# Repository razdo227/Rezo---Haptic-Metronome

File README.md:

# Rezo — Haptic Metronome

A hardware + firmware + mobile app capstone project for a wearable haptic metronome.

## Architecture (at a glance)

```text
Mobile App (Expo / React Native)
  └─ Controls: BPM, transport, sync mode, tap tempo, vibration type
  └─ Sync Modes: INTERNAL | MIDI_CLOCK | MIDI_BEAT
            │
            ├── BLE GATT
            │
Desktop Plugin (JUCE VST3/AU) + Rezo Helper
  └─ DAW transport -> helper IPC -> BLE GATT
  └─ Defaults device mode to MIDI_CLOCK on desktop connect
            │
            ▼
nRF52840 wearable firmware
  └─ Real-time haptic scheduler
  └─ INTERNAL / MIDI_CLOCK / MIDI_BEAT runtime modes
  └─ Dual-LRA drive path (DRV2605L x2)
  └─ Side routing + polyrhythm scheduling
            │
            ▼
Custom PCB + wearable enclosure
```

## Repo layout

- `app/` — cross-platform app (Expo/React Native)
  - `app/src/screens/MainScreen.tsx` — main device-control UI
  - `app/src/context/DeviceContext.tsx` — BLE state + status parsing
  - `app/src/services/BLEService.ts` — BLE transport
  - `app/src/lib/tempo.ts` — tap/BPM logic
  - `app/tests/` — unit tests (Vitest)
- `Kicad Schematics/` — schematic, PCB, and DRC/ERC outputs
- `firmware/` — nRF firmware scaffold + Arduino-ready sketch
- `rezo-plugin/` — JUCE desktop plugin, helper app, and tests
  - `rezo-plugin/Source/` — plugin, helper, BLE bridge, and UI code
  - `rezo-plugin/Tests/` — Catch2 protocol and transport tests
  - `rezo-plugin/JUCE/` — JUCE submodule
- `fab/` — manufacturing files (Gerbers, drill, ZIP)
- `docs/` — project specs, workflows, and engineering notes

## Current status

- App: BLE control surface for INTERNAL / MIDI_CLOCK / MIDI_BEAT modes; `SIDE`/`POLY` commands wired up
- Firmware: dual-LRA scheduler; DRV2605L auto-calibrated for Vybronics VLV101040A; 16 defined waveform patterns
- Desktop: JUCE VST3/AU plugin; 7 presets now match mobile display names; unified via `GATTConstants.h`
- Tests: app unit tests and plugin Catch2 suite
- PCB: v0.1 DRC cleaned to non-critical warnings + Gerbers exported

## Build matrix

| Workstream | Status | Notes |
|---|---|---|
| Mobile App | In Progress | BLE control path is in place; desktop parity still ongoing |
| Firmware | In Progress | Desktop/app protocol implemented; hardware tuning continues |
| Desktop Plugin | In Progress | Helper-based BLE path working in DAWs |
| PCB (v0.1) | In Progress | DRC stabilized; fabrication files generated |
| Validation | In Progress | Unit tests passing; HIL tests pending |
| Research Study | Planned | Protocol and analysis pipeline outlined |

## Run app locally

```bash
cd app
npm install
npm run start
```

## Validate app logic

```bash
cd app
npm test
npx tsc --noEmit
```

## Build desktop plugin

```bash
cd rezo-plugin
cmake -S . -B build/debug -DCMAKE_BUILD_TYPE=Debug
cmake --build build/debug --config Debug
ctest --test-dir build/debug -C Debug --output-on-failure
```

## Next priorities

1. Add app-side UI controls for side routing and polyrhythms (commands wired, UI pending).
2. Hardware-in-loop tests for timing jitter and haptic response.
3. Publish the desktop/helper workflow and host compatibility notes.
4. Validate LRA auto-calibration results on hardware (check `A_CAL_COMP`/`A_CAL_BEMF` registers post-boot).

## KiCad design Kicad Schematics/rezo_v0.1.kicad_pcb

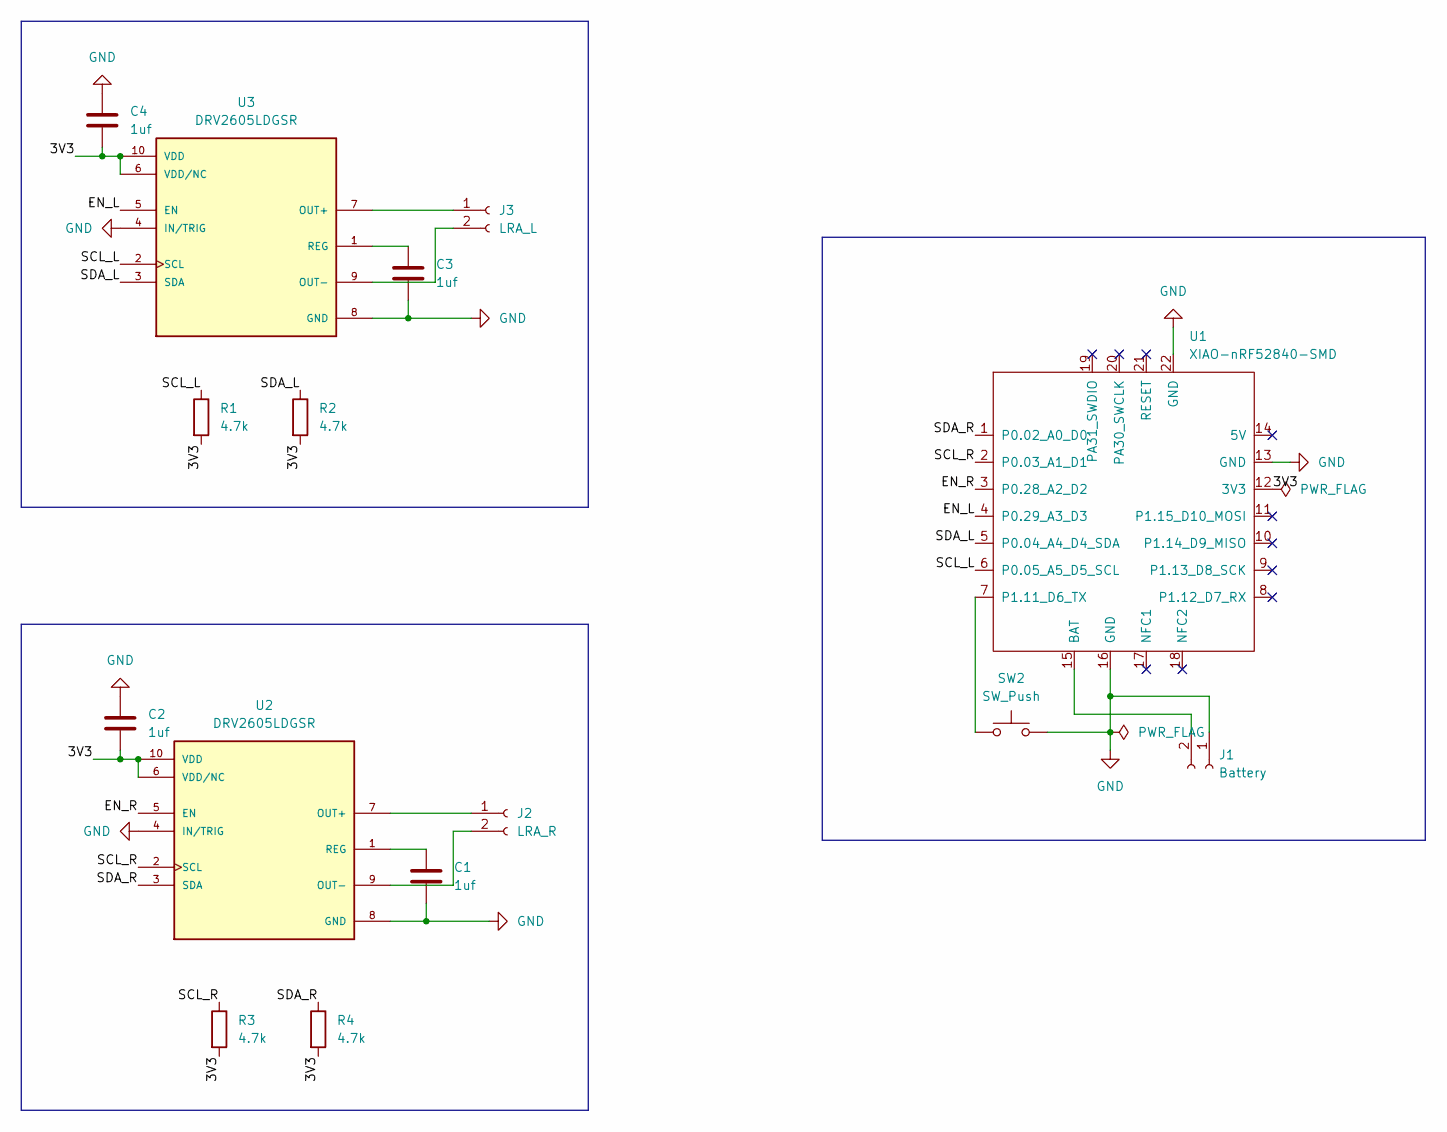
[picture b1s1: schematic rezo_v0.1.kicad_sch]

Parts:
C1, C2, C3, C4: 1uf; C_0603_1608Metric
J1: Battery; SolderWire-0.1sqmm_1x02_P3.6mm_D0.4mm_OD1mm
J2: LRA_R; BOURNS_70AAJ-2-M0
J3: LRA_L; BOURNS_70AAJ-2-M0
R1, R2, R3, R4: 4.7k; R_0603_1608Metric
SW2: SW_Push; SW_SPST_B3S-1000
U1: XIAO-nRF52840-SMD
U2, U3: DRV2605LDGSR; PARTREV D

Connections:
/3V3: C2.2, C4.2, R1.2, R2.2, R3.2, R4.2, U1.12 (3V3), U2.6 (VDD/NC), U2.10 (VDD), U3.6 (VDD/NC), U3.10 (VDD)
/EN_L: U1.4 (P0.29_A3_D3), U3.5 (EN)
/EN_R: U1.3 (P0.28_A2_D2), U2.5 (EN)
/SCL_L: R1.1, U1.6 (P0.05_A5_D5_SCL), U3.2 (SCL)
/SCL_R: R3.1, U1.2 (P0.03_A1_D1), U2.2 (SCL)
/SDA_L: R2.1, U1.5 (P0.04_A4_D4_SDA), U3.3 (SDA)
/SDA_R: R4.1, U1.1 (P0.02_A0_D0), U2.3 (SDA)
GND: C1.2, C2.1, C3.2, C4.1, J1.1, SW2.2, U1.13 (GND), U1.16 (GND), U1.22 (GND), U2.4 (IN/TRIG), U2.8 (GND), U3.4 (IN/TRIG), U3.8 (GND)
unnamed: J1.2, U1.15 (BAT)
unnamed: J2.1, U2.7 (OUT+)
unnamed: J2.2, U2.9 (OUT-)
unnamed: J3.1, U3.7 (OUT+)
unnamed: J3.2, U3.9 (OUT-)
unnamed: SW2.1, U1.7 (P1.11_D6_TX)
unnamed: C1.1, U2.1 (REG)
unnamed: C3.1, U3.1 (REG)

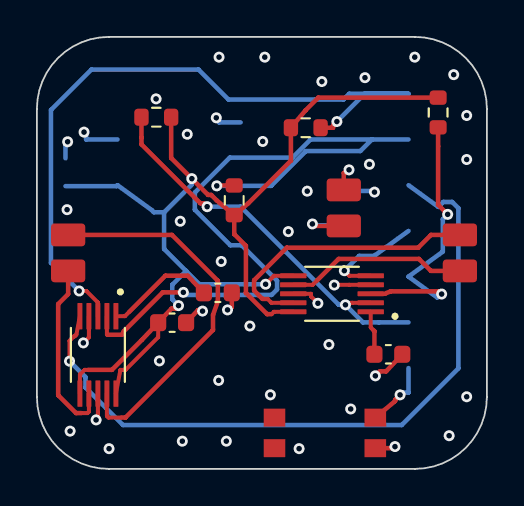
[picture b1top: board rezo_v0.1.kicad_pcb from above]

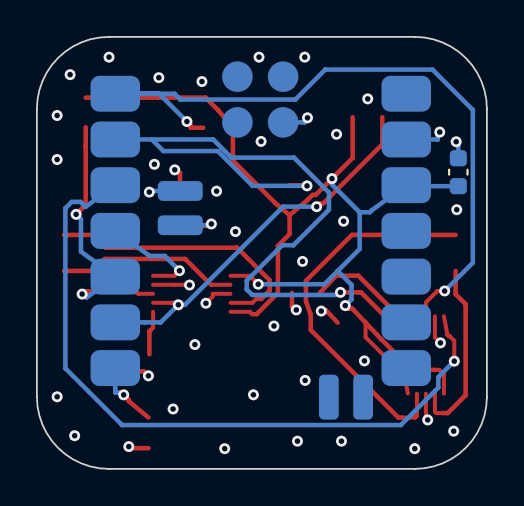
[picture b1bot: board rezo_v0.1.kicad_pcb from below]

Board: 4 copper layers, 25.0 x 24.0 mm, 15 parts (2 on the bottom side), 16 nets.

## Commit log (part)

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2026-01-13 Update project title format in README
2026-01-13 Update project title in README
2026-03-03 Add project operating system and fact-check protocol
2026-03-03 Add KiCad schematic/PCB next-step checklist for v0.2
2026-03-03 Add v0.1 2-layer/4-layer KiCad + JLC manufacturing playbook
2026-03-04 Tune KiCad DRC constraints and mask settings; generate DRC/ERC reports
2026-03-04 Clean silkscreen DRC warnings; reduce board DRC to library-only warnings
2026-03-11 Scaffold cross-platform app v0.1 and add firmware+app feature spec with mic tap tempo
2026-03-11 Add BLE/MIDI/mic-ready app architecture with tested tempo, MIDI clock, and onset logic
2026-03-11 Remove node_modules from tracking and add ignore rules
2026-03-11 Add nRF clock-master sync modes with MIDI beat-trigger state machine and tests
2026-03-12 Polish app UI with professional minimal design system and tokenized theme
2026-03-12 Trim hero copy and add vibration type selector in app UI
2026-03-12 Refactor top section into compact status header with less redundancy
2026-03-12 Add architecture-focused README with repo map and next steps
2026-03-12 Polish README with conservative badges and compact build matrix
2026-03-12 Start nRF firmware scaffold with sync-mode runtime and BLE command protocol skeleton
2026-03-12 Add Arduino-ready XIAO nRF52840 firmware sketch for DRV2605 with BLE control
2026-03-12 Add multi-pattern haptics in firmware and wire app BLE commands to device protocol
2026-03-12 Stabilize Expo entrypoint, BLE transport wiring, and EAS build config
2026-03-12 Ship crash-safe Android build path with mock transport startup
2026-03-12 Rebuild app with explicit BLE pairing screen, manual device selection, and placeholder icons
2026-03-12 Force JSC runtime for Android stability in release builds
2026-03-13 firmware: add pairing LED pattern and startup haptic cue
2026-03-13 Implement stable BLE-first mobile controller flow
2026-03-13 Add Android native project files to repo (Expo prebuild output)
2026-03-15 Refactor code structure
2026-03-15 feat: Initialize iOS project with CocoaPods dependencies and update application configuration.
2026-03-30 fix: resolve dual-version merge conflicts and compilation errors
2026-03-30 fix: use Seeeduino:mbed core — restore MbedI2C, correct AR_INTERNAL2V4
2026-03-30 fix: switch to LRA mode (useLRA + library 6) for VLV101040A motors, fix waveform slot clearing
2026-03-30 fix: remove useLRA() closed-loop tracking, keep library 6
2026-03-30 fix: use LRA open-loop mode at 175Hz for VLV101040A — stable without calibration
2026-03-30 feat: consolidate app, firmware, and desktop plugin
2026-03-31 Refine tempo UI to better match provided mobile mock

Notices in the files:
README.md:
License: MIT
